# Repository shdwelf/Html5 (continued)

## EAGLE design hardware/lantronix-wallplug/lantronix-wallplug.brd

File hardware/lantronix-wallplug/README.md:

# xPort Wallplug — a mains-powered RS-232 ↔ Ethernet adapter around a Lantronix xPort Pro

Generated EAGLE design. **Do not edit these files by hand** — they are emitted from
[`tools/wallplug-model.mjs`](../../tools/wallplug-model.mjs) by
[`tools/build-wallplug-eagle.mjs`](../../tools/build-wallplug-eagle.mjs), and every claim below is re-checked by
that generator.

```bash
node tools/build-wallplug-eagle.mjs            # regenerate .lbr/.sch/.brd + BOM.md
node tools/build-wallplug-eagle.mjs --check    # regenerate, then verify (non-zero exit on failure)
node tests/20-wallplug.mjs                     # 276 assertions over the generated files and the model
```

Current state of `--check`:

```
lantronix-wallplug.lbr: 46381 bytes, 21 packages, 19 symbols, 21 devicesets
lantronix-wallplug.sch: 86035 bytes, 1 sheet, 42 instances, 41 nets
lantronix-wallplug.brd: 71843 bytes, 46 elements, 147 pads
worst mains↔SELV creepage: 10.04 mm (MOV1.2 ↔ PS1.4), limit 6.4 mm
schematic: 42 instances on a 480 × 300 mm sheet, no overlapping label boxes
OK — XML well-formed, every reference resolves, connectivity matches the model, geometry clean.
```

Open it in [Lantronix Lab → WALLPLUG EDA](../../lantronix-lab.html#eda) to see the board and the schematic
rendered in the browser, with the same design rules re-run client-side.

## Files

| File | Contents |
| --- | --- |
| `lantronix-wallplug.lbr` | Design library: 21 packages (including the xPort Pro module footprint and the HLK-PM03), 19 symbols, 21 devicesets |
| `lantronix-wallplug.sch` | One sheet, 480 × 300 mm, 42 instances, label-driven wiring (every pin carries a net label and a 5.08 mm stub) |
| `lantronix-wallplug.brd` | 110 × 64 mm, two layers, 46 placed elements, 41 signals with contact refs, mains/SELV barrier on tPlace + tRestrict, ground pour confined to the SELV half |
| `BOM.md` | Bill of materials with DNP flags and zones, plus the full netlist and the safety section |

EAGLE version is written as `9.6.2`. The XML grammar follows the EAGLE DTD as documented inside KiCad's importer
(`common/io/eagle/eagle_parser.h`), so `File → Import → Non-KiCad Project → EAGLE` in a current KiCad is a
second, independent way to prove the files are real.

## What it is

A wallplug that turns a bare **Lantronix xPort Pro** module (16 MB flash, 8/16 MB SDRAM, ColdFire, Linux/µClinux
or Evolution OS) into a mains-powered serial-to-Ethernet adapter — functionally the EDS1100 in a smaller box:

```
mains ── J1 ── F1 (T500 mA, line only) ──┬── PS1 HLK-PM03 (isolated 3.3 V / 3 W) ── FB1 ── 3V3
                                          └── MOV1 (S07K275, after the fuse)              │
                                                                                          ▼
   DE-9 (J2, DTE by default) ── U2 MAX3232 ── 3.3 V CMOS ── X1 xPort Pro ── RJ45 (through the board edge)
   field terminal (J3) ────────────────────────┘              │
   TTL header (J4: 3V3 GND TXD RXD CP1 CP2 CP3 RESET DSR GND) ┘
```

Options, all DNP by default: **U3** a second MAX3232 for real ±RS-232 modem control (RTS/CTS/DTR/DCD), and
**U4** an SP3485 + three 0 Ω links for the RS-485 front end the Integration Guide's appendix A describes.
Fit one front end at a time — RS-232 and RS-485 share the module's TTL pins.

## Design rules the generator enforces

* **Creepage 6.4 mm / clearance 4.0 mm** between every mains pad and every SELV pad, measured pad-edge to
  pad-edge. The AC/DC converter's pads are zone-tagged individually, so its 3.3 V output may sit close to the
  logic while its AC pins may not.
* **No courtyard may overlap** another (0.2 mm tolerance) or leave the outline — except parts flagged `edge`
  (the DE-9 and the module's RJ45 nose both mate through the board edge).
* **Pad-to-pad ≥ 0.35 mm** edge-to-edge unless the pads share a net or a package. SMD pads are compared as
  rotation-corrected rectangles, so a legal 1.27 mm SOIC pitch is not reported as a collision, while a real
  collision between two packages is.
* **Ground pour is confined** to x ≥ 52 mm, so copper cannot bridge the barrier at x = 50 mm.
* **Mounting holes** keep 3.2 mm from every pad.
* **Sheet readability:** no two instance label boxes may overlap, and none may run off the sheet.

## Routing (left to the builder, deliberately)

The board is placed, verified and netlisted, **not routed**. On a mains board, routing is where the safety
decisions actually live, so they are written down instead of generated:

* Mains: ≥ 2.5 mm tracks, net class 1 (`mains`, 6.4 mm clearances). L through F1 then to PS1 pin 1; N straight to
  PS1 pin 2; MOV1 last, so a varistor failure opens the fuse.
* 3.3 V: ≥ 1.0 mm from FB1 to the module's pin 2 (class 2, `power`), with C1/C2/C3/C4 as close to the pin field
  as they fit. The module draws 200 mA typical / 270 mA max at 100Base-TX on Linux; the HLK-PM03's ~600 mA
  continuous rating has margin but no slack for a long thin trace.
* Serial: keep the DE-9's TXD/RXD pair on the far side of the module from PS1's switching node.
* Shield tabs: at least **1 in² (6.45 cm²)** of copper — the Integration Guide calls them "an important source of
  heat sinking", and the module is rated to +85 °C only with it.

## Assembly and bring-up

1. Fit the power section only. With no module installed, verify 3.3 V ±2 % and ≤ 2 % ripple at the module header
   (the guide's recommended operating conditions), and note the reset thresholds: 2.85–3.00 V supply reset,
   internal 140 ms power-up reset, power-drop reset at 2.95 V.
2. Fit X1. Connect a **3.3 V** USB-serial adapter to J4 — never RS-232 levels to the TTL header, and remember
   that no module pin is 5 V tolerant. Look for the dBUG banner at 115200 8N1.
3. Fit U2 and J2/J3. Check the DTE/DCE straps: JP1/JP2 at 1-2 = **DTE** (EDS2100 style, the default),
   at 2-3 = **DCE** (UDS1100 style).
4. Only then consider U3 or U4 + R8/R9/R10.

## Safety, honestly

* This is a **design study**. It has not been certified, and mains-connected PCBs need an IEC/EN 62368-1 (or
  60950-1) assessment plus a properly rated enclosure before anyone plugs one in.
* PS1 is the only isolation barrier. The budget HLK-PM03 is 3 kV-rated but not safety-certified; for a
  user-accessible product use a certified part in the same role (RECOM RAC03-3.3SK, MEAN WELL IRM-03-3.3).
* Fuse in the line conductor only, MOV after the fuse, no reliance on the PCB for basic insulation, class-II
  (all-insulated) enclosure, and the module's chassis tied through the 10 nF / 200 V capacitors the Integration
  Guide recommends rather than bolted to signal ground.
* Nothing here depends on rebuilding the module's firmware. If you do rebuild it, see
  [docs/lantronix-uclinux-deep-dive-2026-10-08.md](../../docs/lantronix-uclinux-deep-dive-2026-10-08.md) §2–§3.

## Provenance of the geometry

| Package | Source |
| --- | --- |
| `XPORTPRO` | Lantronix Integration Guide 900-557 rev K: Table 2-2 (pin functions), Figure 2-7 (hole pattern: 2 × Ø1.60 shield, 8 × Ø0.90 signal, 2 × Ø3.25; pin field 17.20 × 19.74 mm; body 33.90 × 16.26 mm) — cross-checked against `robertstarr/lbr_user lantronix.lbr` (package `XPORT`) and `tridrao/SparkFun-KiCad-Libraries XPORT.kicad_mod` |
| `HLKPM03` | Hi-Link HLK-PM03 (34 × 20 × 15 mm, 3.3 V / 3 W, 85–265 VAC, 3 kV); pin grid from two independent KiCad footprints that agree: AC pair 5.08 mm, DC pair 15.24 mm, rows 29.21 mm |
| `DB9MRA` | KiCad `Connector_Dsub.pretty/DSUB-9_Male_Horizontal_P2.77x2.84mm_EdgePinOffset7.70mm_Housed_MountingHolesOffset9.12mm` (pad grid 2.77 × 2.84, Ø3.2 mounting holes, board edge 7.70 mm from pin row 1) |
| `SO16` / `SO8` | KiCad `Package_SO.pretty/SOIC-16_3.9x9.9mm_P1.27mm` (pad centres ±2.475, pads 1.95 × 0.6) and the 8-pin equivalent |
| `SW-TACT-6MM` | KiCad `Button_Switch_THT.pretty/SW_PUSH_6mm` (pads ±3.25 / ±2.25, Ø1.1 drills) |
| the rest | standard through-hole patterns: DIN0207 axial 7.62 mm, disc capacitor 5.08 mm, radial electrolytics, 5.08 mm screw terminals, 2.54 mm headers, TR5 radial fuse, 7 mm varistor |

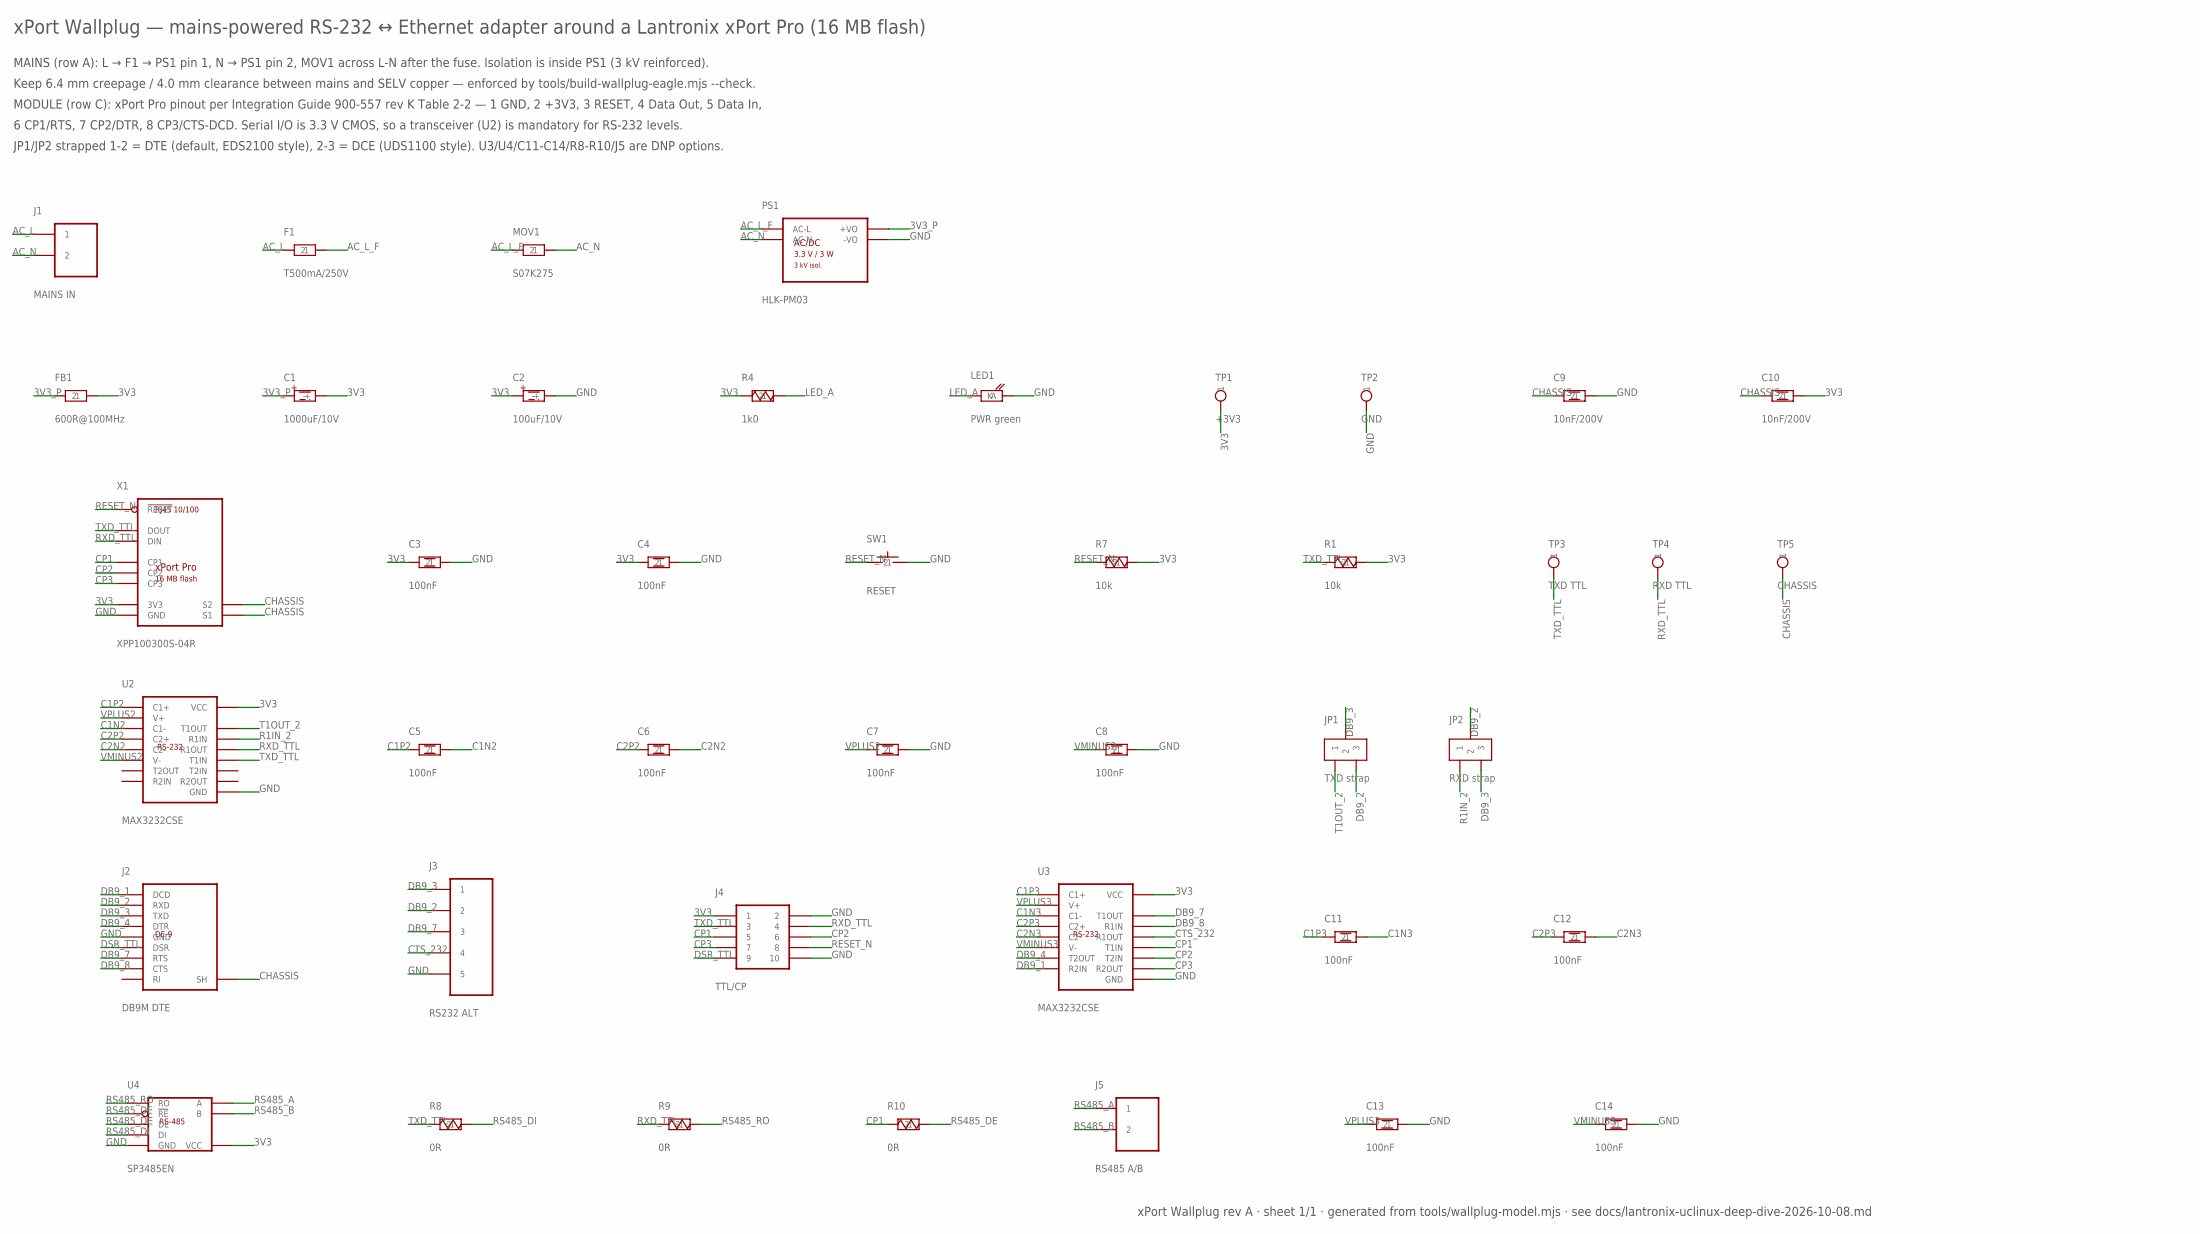
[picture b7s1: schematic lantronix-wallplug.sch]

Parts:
C1: 1000uF/10V; CP-D10-P5
C2: 100uF/10V; CP-D6.3-P2.5
C3, C4, C5, C6, C7, C8, C11, C12, C13, C14: 100nF; C-5.08
C9, C10: 10nF/200V; C-5.08-200V
F1: T500mA/250V; FUSE-RADIAL
FB1: 600R@100MHz; FB-7.62
J1: MAINS IN; TERM2-5.08
J2: DB9M DTE; DB9MRA
J3: RS232 ALT; TERM5-5.08
J4: TTL/CP; HDR-2X5
J5: RS485 A/B; TERM2-5.08
JP1: TXD strap; SJ-3
JP2: RXD strap; SJ-3
LED1: PWR green; LED-5MM
MOV1: S07K275; MOV07
PS1: HLK-PM03; HLKPM03
R1, R7: 10k; R-7.62
R4: 1k0; R-7.62
R8, R9, R10: 0R; R-7.62
SW1: RESET; SW-TACT-6MM
TP1: +3V3; TP
TP2: GND; TP
TP3: TXD TTL; TP
TP4: RXD TTL; TP
TP5: CHASSIS; TP
U2, U3: MAX3232CSE; SO16
U4: SP3485EN; SO8
X1: XPP100300S-04R; XPORTPRO

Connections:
3V3: C1.-, C2.+, C3.1, C4.1, C10.2, FB1.2, J4.1, R1.2, R4.1, R7.2, TP1.1, U2.16 (VCC), U3.16 (VCC), U4.8 (VCC), X1.2 (3V3)
3V3_P: C1.+, FB1.1, PS1.4 (+VO)
AC_L: F1.1, J1.1
AC_L_F: F1.2, MOV1.1, PS1.1 (AC-L)
AC_N: J1.2, MOV1.2, PS1.2 (AC-N)
C1N2: C5.2, U2.3 (C1-)
C1N3: C11.2, U3.3 (C1-)
C1P2: C5.1, U2.1 (C1+)
C1P3: C11.1, U3.1 (C1+)
C2N2: C6.2, U2.5 (C2-)
C2N3: C12.2, U3.5 (C2-)
C2P2: C6.1, U2.4 (C2+)
C2P3: C12.1, U3.4 (C2+)
CHASSIS: C9.1, C10.1, J2.MH (SH), TP5.1, X1.S1, X1.S2
CP1: J4.5, R10.1, U3.11 (T1IN), X1.6 (CP1)
CP2: J4.6, U3.10 (T2IN), X1.7 (CP2)
CP3: J4.7, U3.9 (R2OUT), X1.8 (CP3)
CTS_232: J3.4, U3.12 (R1OUT)
DB9_1: J2.1 (DCD), U3.8 (R2IN)
DB9_2: J2.2 (RXD), J3.2, JP1.3, JP2.2
DB9_3: J2.3 (TXD), J3.1, JP1.2, JP2.3
DB9_4: J2.4 (DTR), U3.7 (T2OUT)
DB9_7: J2.7 (RTS), J3.3, U3.14 (T1OUT)
DB9_8: J2.8 (CTS), U3.13 (R1IN)
DSR_TTL: J2.6 (DSR), J4.9
GND: C2.-, C3.2, C4.2, C7.2, C8.2, C9.2, C13.2, C14.2, J2.5 (GND), J3.5, J4.2, J4.10, LED1.2 (K), PS1.3 (-VO), SW1.2, TP2.1, U2.15 (GND), U3.15 (GND), U4.5 (GND), X1.1 (GND)
LED_A: LED1.1 (A), R4.2
R1IN_2: JP2.1, U2.13 (R1IN)
RESET_N: J4.8, R7.1, SW1.1, X1.3 (!RESET)
RS485_A: J5.1, U4.6 (A)
RS485_B: J5.2, U4.7 (B)
RS485_DE: R10.2, U4.2 (!RE), U4.3 (DE)
RS485_DI: R8.2, U4.1 (DI)
RS485_RO: R9.2, U4.4 (RO)
RXD_TTL: J4.4, R9.1, TP4.1, U2.12 (R1OUT), X1.5 (DIN)
T1OUT_2: JP1.1, U2.14 (T1OUT)
TXD_TTL: J4.3, R1.1, R8.1, TP3.1, U2.11 (T1IN), X1.4 (DOUT)
VMINUS2: C8.1, U2.6 (V-)
VMINUS3: C14.1, U3.6 (V-)
VPLUS2: C7.1, U2.2 (V+)
VPLUS3: C13.1, U3.2 (V+)

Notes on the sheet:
xPort Wallplug — mains-powered RS-232 ↔ Ethernet adapter around a Lantronix xPort Pro (16 MB flash)
MAINS (row A): L → F1 → PS1 pin 1, N → PS1 pin 2, MOV1 across L-N after the fuse. Isolation is inside PS1 (3 kV reinforced).
Keep 6.4 mm creepage / 4.0 mm clearance between mains and SELV copper — enforced by tools/build-wallplug-eagle.mjs --check.
MODULE (row C): xPort Pro pinout per Integration Guide 900-557 rev K Table 2-2 — 1 GND, 2 +3V3, 3 RESET, 4 Data Out, 5 Data In,
6 CP1/RTS, 7 CP2/DTR, 8 CP3/CTS-DCD. Serial I/O is 3.3 V CMOS, so a transceiver (U2) is mandatory for RS-232 levels.
JP1/JP2 strapped 1-2 = DTE (default, EDS2100 style), 2-3 = DCE (UDS1100 style). U3/U4/C11-C14/R8-R10/J5 are DNP options.
xPort Wallplug rev A · sheet 1/1 · generated from tools/wallplug-model.mjs · see docs/lantronix-uclinux-deep-dive-2026-10-08.md

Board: 2 copper layers, 46 parts (0 on the bottom side), 41 nets, no tracks yet.

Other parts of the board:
H1, H2, H3, H4: MOUNT-M3
